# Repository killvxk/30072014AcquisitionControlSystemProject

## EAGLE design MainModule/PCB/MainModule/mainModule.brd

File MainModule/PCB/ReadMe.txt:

Main Module
PCB + Schematics (Eagle)

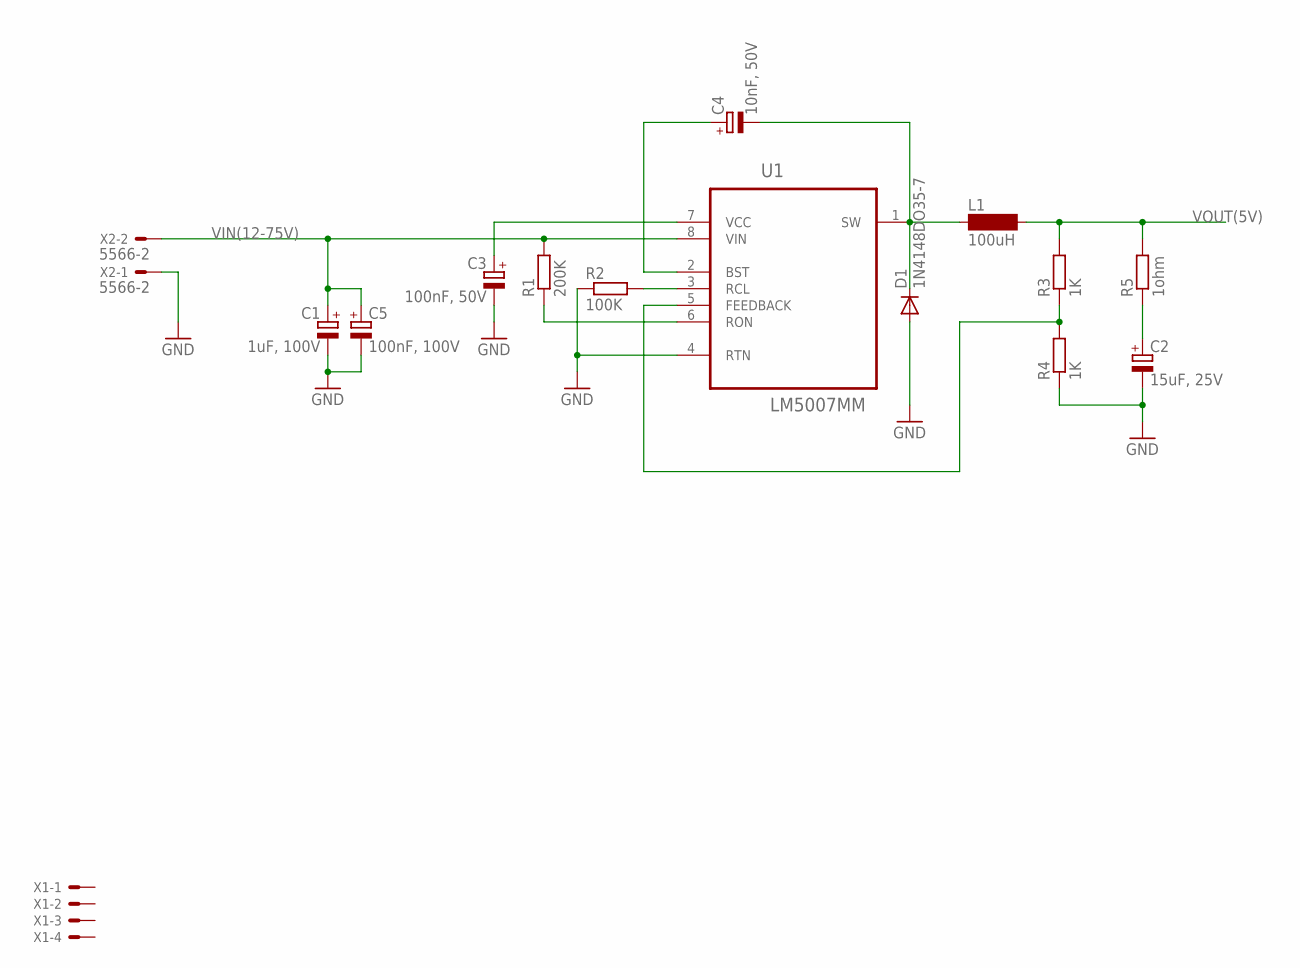
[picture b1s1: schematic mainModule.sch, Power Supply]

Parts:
C1: 1uF, 100V; 153CLV-0405
C2: 15uF, 25V; PANASONIC_C
C3: 100nF, 50V; SMC_A
C4: 10nF, 50V; R/2012-12W
C5: 100nF, 100V; SMC_A
D1: 1N4148DO35-7; DO35-7
L1: 100uH; SM-Z15
R1: 200K; R2010
R2: 100K; R2010
R3, R4: 1K; R2010
R5: 1ohm; R2010
U1: LM5007MM; SOP65P490X109-8N
X1: KK-156-4
X2: 5566-2

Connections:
GND: C1.-, C2.-, C3.-, C5.-, D1.A, R2.1, R4.1, U1.4 (RTN), X2.1
unnamed: R2.2, U1.3 (RCL)
unnamed: R1.1, U1.6 (RON)
unnamed: C4.+, U1.2 (BST)
unnamed: C4.-, D1.C, L1.1, U1.1 (SW)
unnamed: C3.+, U1.7 (VCC)
unnamed: R3.1, R4.2, U1.5 (FEEDBACK)
unnamed: C2.+, R5.1
VIN(12-75V): C1.+, C5.+, R1.2, U1.8 (VIN), X2.2
VOUT(5V): L1.2, R3.2, R5.2

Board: 2 copper layers, 15 parts (0 on the bottom side), 10 nets, no tracks yet.

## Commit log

2014-08-05 Folder Structure Of the Project
2014-08-20 Added datasheet of electronic components.
2014-08-21 Reorganization of the Datasheets.
2014-08-21 Added new comment in ReadMe files. Refer to module group name.
2014-08-21 Created Eagle projects for all of modules.
2014-08-21 Added Libraries for electronic components in the PCB/Libraries location for all modules.
2014-08-25 :confetti_ball: Added .gitattributes & .gitignore files
2014-08-26 LN5007 mark text lines
2014-08-28 added mainModule schematic with power supply components
2014-08-28 Rename the PCB folder "Main Module" to "MainModule"
2014-08-28 Rename folder "Control Expansino Module" to "ControlExpansionModule"
2014-08-28 Folder Rename
    renaming the folder
2014-08-28 Rename folder 'Acquisition Expansion Module' to 'AcquisitionExpansionModule'
2014-08-28 Created power supply circuit
2014-08-29 changed output voltage form switching power supply
2014-08-29 Added mainModule.brd file to the project
2014-08-29 Changed capacitor packages in to power supply schematic (switching)
2014-08-29 Added linear regulator LM3940.lbr library
2014-08-29 Wiring circuit for liner regulator (LM3940)
2014-08-29 Added LPCXpresso boards library
2014-08-29 Summary: - added Lpcxspresso board to the project(LPC1769) - wiring switching power supply - wiring liner regulator - added miniUSB connector - added MOLEX connector - added powerIN connector
2014-08-30 Created New module branch in the concept (Power Supply Module)
2014-08-30 Folder PowerSupplymodule is deleted
2014-08-30 Folder is added for new module branch (power supply module)
2014-08-30 Replacing schematic for switching supply in to new document PowerSupplyModule/PCB/powerSupplyModule.sch
2014-08-30 replaced schematic for switching power supply in new document
2014-08-30 Replaced library form MainModule to PowerSupplyModule and created new Eagle project in location PowerSupplyModule/PCB/PM-LM5007/eagle.epf
2014-08-31 Added a schematic file for Control Expansion module, based on PCA9557
2014-08-31 Wired schematic for port expander, based on PCA9557
2014-08-31 Added files to ignore list
2014-09-01 Created new schematic file for Expansion Control Module PCF8574 based
2014-09-01 Added component in the circuit
2014-09-01 Wiring components in the Port expander circuit based on PCF8574
2014-09-01 Repair Libraries/PCF8575.lbr - wrong footprint
2014-09-01 Created schematic file for Port Expander PCF8575 based (16bit)
2014-09-01 Wiring component of the circuit of Port Expansion Module, based on PCF8575
2014-09-01 Wiring components of the circuit of Port Expansion Module, based on PCF8575
2014-09-03 Added static libraries for LPC1769 project (board and USB libraries)
2014-09-03 Added MainModule(LPC1769) source project
2014-09-04 ignore files
2014-09-04 Added Ignored files
2014-09-04 Reorganize
2014-09-04 Added file to the ignore list
2014-09-04 added 3rd party codes to the project
2014-09-05 Removed comment
2014-09-18 Added ADS1231 library, and porting interface ports. P0.8 - CLK P0.9 - DATA
2014-10-24 Added schematic for Acquisition Expansion Module... (ADS1015 based)
2014-10-25 designing PCB
    designing PCB, edit schematic
